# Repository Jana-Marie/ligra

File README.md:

# ligra

ligra is an open source image projector build from scratch and based off of flea market parts. ligra is not neccessarily a PCB-project nor a single thing, but rather an idea of how to design your own image-projection system. It is an introduction on how to create light-grafittis, how to share messages at large.

It's not strictly a Gobo, rather a way of building a system that may resemble one, but may also resemble a video projector or an abstract source of art. I have mostly used it with 2D printed stencils, usually used with so called "overhead projectors", one can of course also use metal-stencils, coloured effect-foils, 3D printed stencils and even LCDs, or really anything that may project an image. Get creative! 

<table>
  <tbody>
    <tr>
      <td>
        
      </td>
      <td>
        
      </td>
    </tr>
    <tr>
      <td colspan="2">
        
      </td>
    </tr>
  </tbody>
</table>

This repo is very WIP and shall be expanded soon :3

## Working principle

ligra essentially functions as a backwards camera, well, most projectors do. This becomes more visible when we talk about its inner workings, it's heart and most fixed element is the lens, a Canon FD lens in our case. But instead of using it to project and image **onto** a 35mm film slide, we will project light **through** a ruffly 35mm film slide-sized, image forming medium (i.e. a 2D printed stencil). This light will enter the lens from the back, projecting an image onto a scene with the properties of the lens (focal length, aperture and focus). Given the quality of even early lenses, we can expect some sharp and crisp projections. [WIP ...]

## [Instructions](https://github.com/Jana-Marie/ligra/blob/main/instructions.md)

(Want to build one? ^ click me)

<table>
  <tbody>
    <tr>
      <td>
        
      </td>
    </tr>
  </tbody>
</table>

## [Projection-Media](https://github.com/Jana-Marie/ligra/blob/main/projection-media.md)

(You have one and need stencils? ^ click me)

<table>
  <tbody>
    <tr>
      <td>
        
      </td>
      <td>
        
      </td>
      <td>
        
      </td>
    </tr>
  </tbody>
</table>

## [Staging-Stages](https://github.com/Jana-Marie/ligra/blob/main/staging-stages.md)

(You have one and want to work on a different stage, a different way of adding media for projection? ^ click me)

<table>
  <tbody>
    <tr>
      <td>
        
      </td>
      <td>
        
      </td>
      <td>
        
      </td>
    </tr>
  </tbody>
</table>

## Todo

- [ ] Add assembly instructions (85% done)
  - [ ] Refine by adding real images (45% done)
- [ ] Add 3D print instructions (5% done)
- [ ] Add BOM (0% done)
- [ ] Add drawings (60% done)
- [x] Make projection-media page more expressive
- [x] Design more stages
- [x] Cleanup OpenSCAD file

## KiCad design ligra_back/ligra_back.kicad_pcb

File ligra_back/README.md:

# Back-Board

This board serves as power-input and LED controller for a 0-3A 0-5V LED. It currently is v1.0.0 and has an additional DC-motor speed controller onboard, you can safely ignore it. I plan to build a different version for myself, that is a bit more advanced, feel free to then also use it. Generally this board is fully optional, but may prove to be very useful.

<table>
  <tbody>
    <tr>
      <td>
        
      </td>
      <td>
        
      </td>
    </tr>
  </tbody>
</table>

[Todo, add BOM and assembly instructions here]

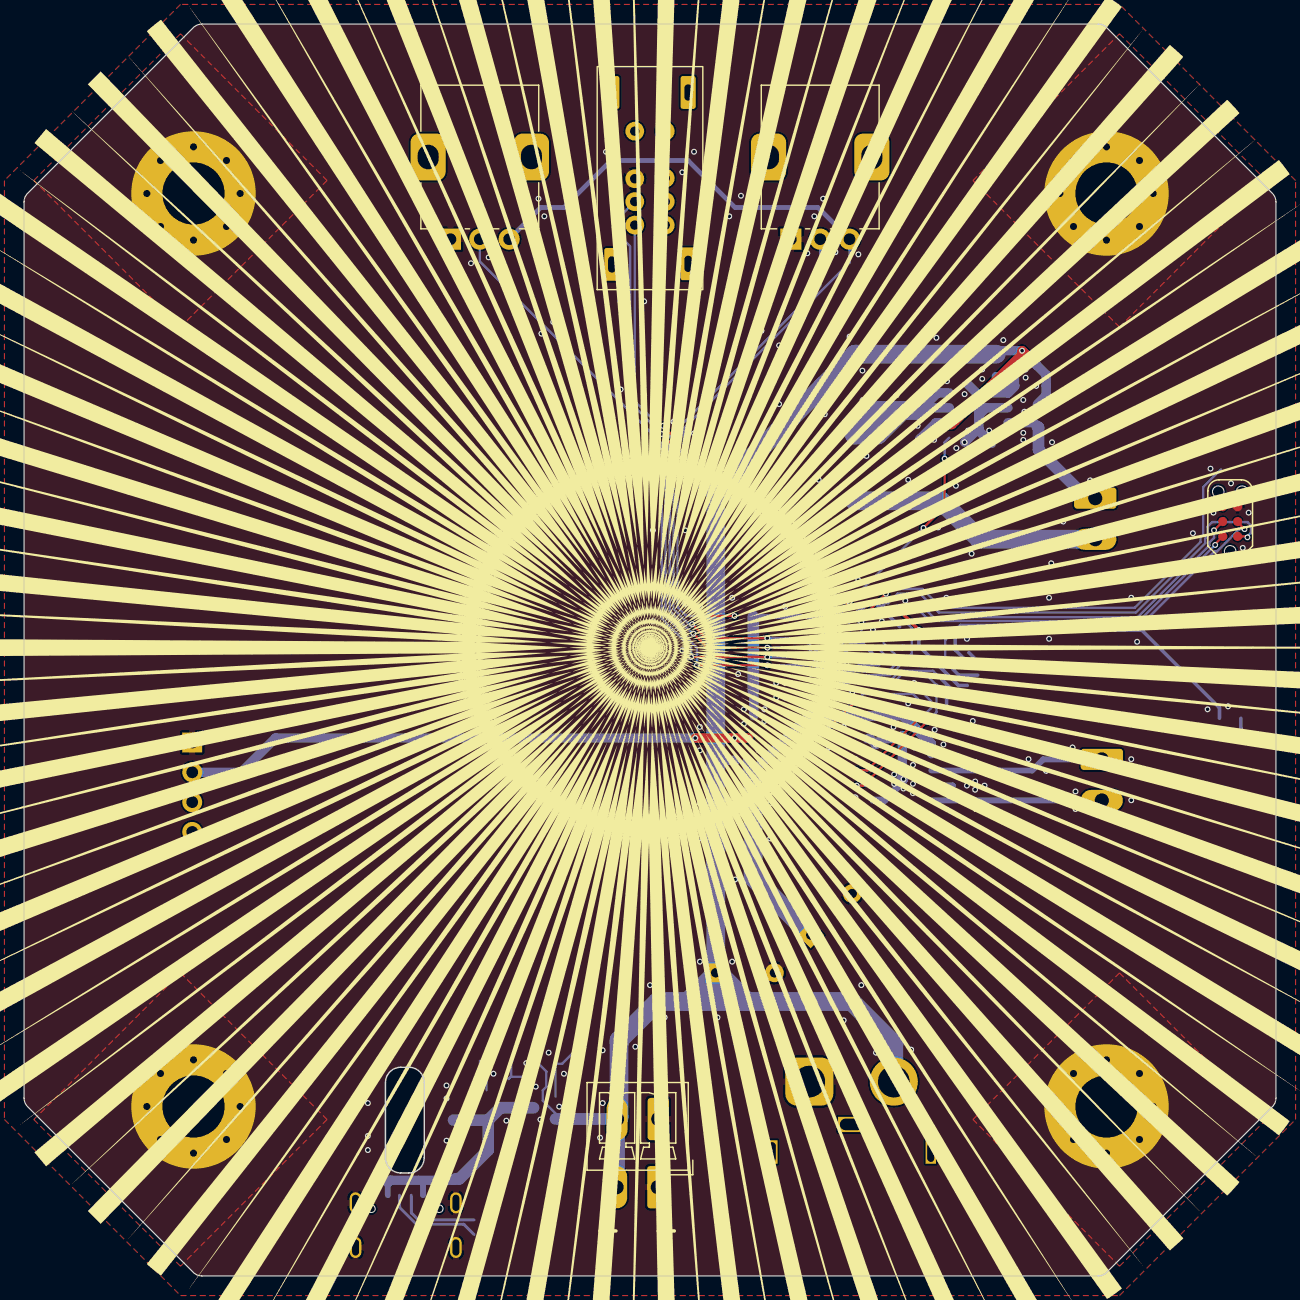
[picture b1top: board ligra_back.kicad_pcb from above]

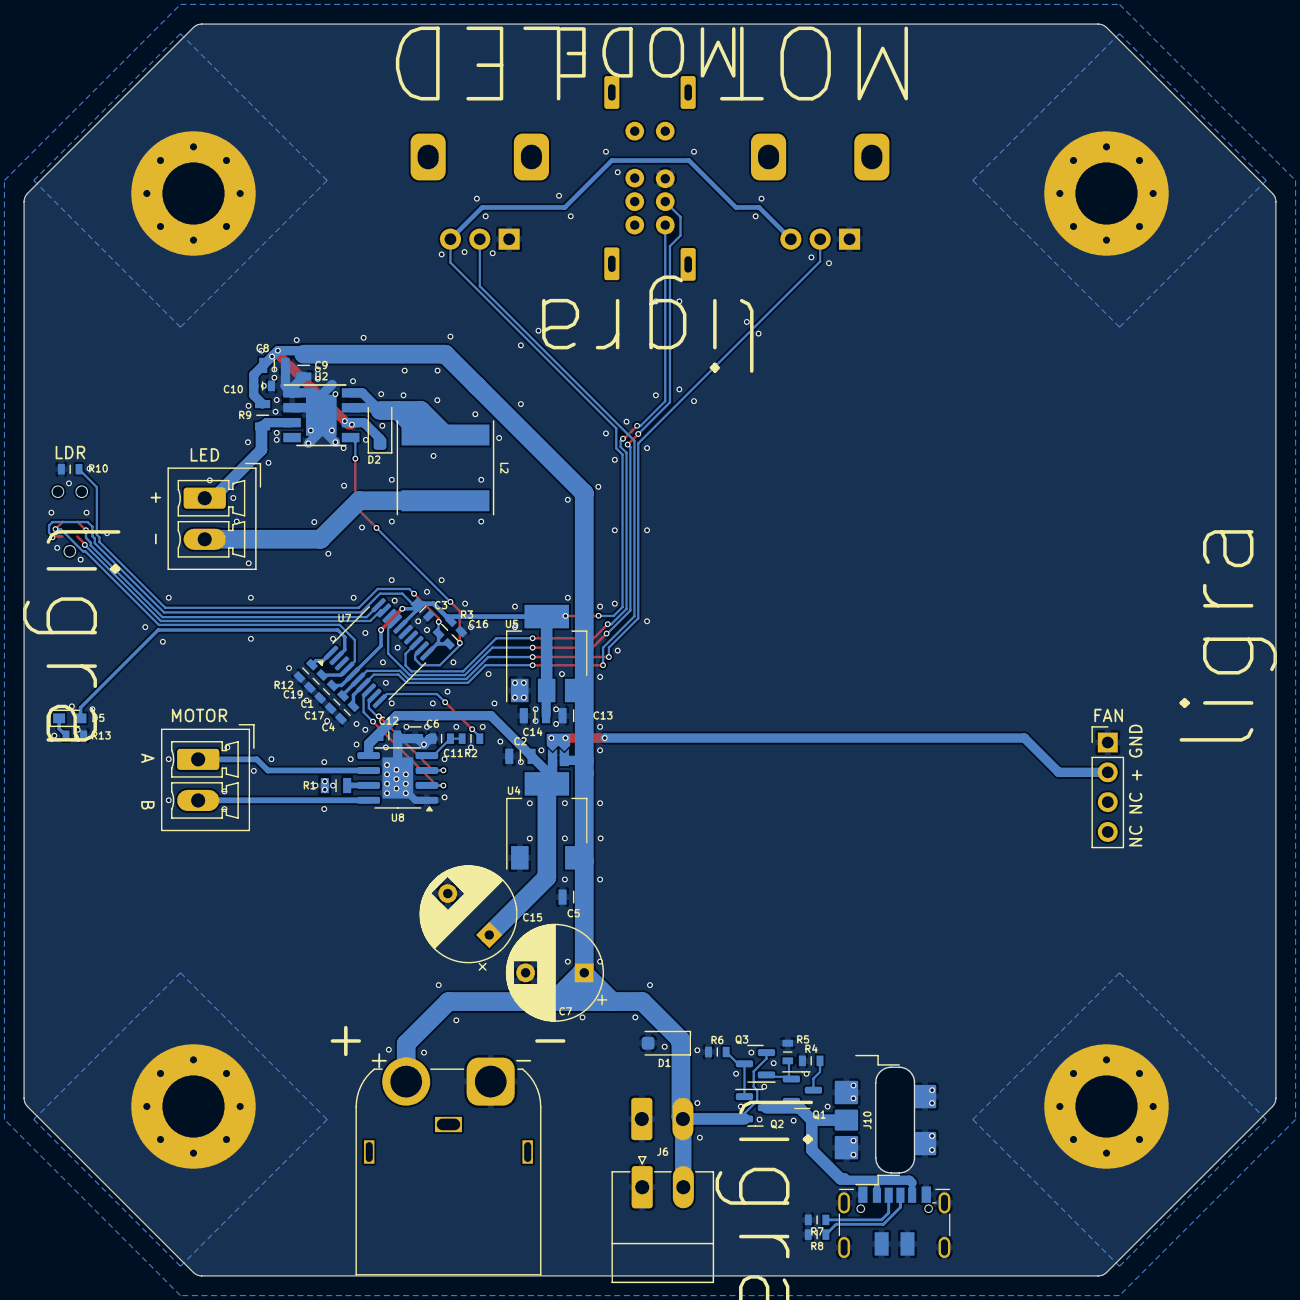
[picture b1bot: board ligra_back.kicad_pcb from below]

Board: 2 copper layers, 106.7 x 106.7 mm, 59 parts (50 on the bottom side), 33 nets.

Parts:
C1, C3, C4, C10, C11, C12, C16, C17, C19: 100n; C_0603
C2, C5, C6, C8, C9, C13, C14: 4u7; C_0805
C7, C15: 100u; CP_Radial_D8.0mm_P5.00mm
D1, D2: D210; D_SOD-123F
D5: LED; LED_0603_1608Metric
J1, J2, J3, J4: Mount; MountingHole_5.3mm_M5_Pad_Via
J5: POWER; PhoenixContact_MCV_1,5_2-G-3.5_1x02_P3.50mm_Vertical
J6: POWER; PhoenixContact_MC_1,5_2-G-3.5_1x02_P3.50mm_Horizontal
J7: LED; PhoenixContact_MCV_1,5_2-G-3.5_1x02_P3.50mm_Vertical
J8: FAN; PinHeader_1x04_P2.54mm_Vertical
J9: Motor; PhoenixContact_MCV_1,5_2-G-3.5_1x02_P3.50mm_Vertical
J10: USB-vertical_footprint; USB-C-vertical_footprint
J11: USB_C_Receptacle_PowerOnly_6P; USB-C_Power
J12: XT60; AMASS_XT60IPW-M_1x03_P7.20mm_Horizontal
JP1: jmp; JMP_2_1
L2: 47uF; L_Taiyo-Yuden_NR-80xx
P1: TC2030-CTX-Tag-Connect; TC2030
Q1, Q3: BC807; SOT-23
Q2: AO3401A; SOT-23
R1, R9: R33; R_0805
R2, R3, R4, R5, R6, R7, R8, R12, R13: 5k1; R_0603
R10: LDR; R_0603
RV1, RV2: 10k; Potentiometer_Alps_RK09K_Single_Vertical
SW2: SW_SP3T; SW_3S
U2: AL8843; Diodes_SO-8EP
U4: NCP1117-12_SOT223; SOT-223-3_TabPin2
U5: NCP1117-3.3_SOT223; SOT-223-3_TabPin2
U7: STM32F030F4Px; TSSOP-20_4.4x6.5mm_P0.65mm
U8: DRV8231; SOIC-8-1EP_3.9x4.9mm_P1.27mm_EP2.62x3.51mm

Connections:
+3V3: C1.2, C3.2, C14.2, P1.1 (VCC), R3.2, RV1.3, RV2.3, U5.2 (VO), U7.5 (VDDA), U7.16 (VDD)
+12V: C2.2, C6.2, C12.1, C15.1, JP1.1 (A), U4.2 (VO), U8.5 (VM)
GND: C1.1, C2.1, C3.1, C4.1, C5.1, C6.1, C7.2, C8.1, C9.1, C10.1, C11.1, C12.2, C13.2, C14.1, C15.2, C16.1, C17.1, C19.1, D1.2 (A), J1.1, J2.1, J3.1, J4.1, J5.1, J6.1, J8.1, J10.1 (GND), J10.S1 (GND), J11.A12 (GND), J11.B12 (GND), J11.S1 (SHIELD), J12.1, P1.5 (GND), R1.2, R4.1, R5.1, R6.1, R7.2, R8.2, R10.1, R12.1, R13.1, RV1.1, RV2.1, SW2.3, U2.1 (GND), U2.2 (GND), U2.9 (GND), U4.1 (GND), U5.1 (GND), U7.15 (VSS), U8.1 (GND), U8.9 (GND)
LED_CONTROL: U2.5 (CTRL), U7.12 (PA6)
NRST: C19.2, P1.3 (~RESET), U7.4 (NRST)
unnamed: D2.2 (A), L2.1, U2.7 (SW), U2.8 (SW)
unnamed: D5.2 (A), U7.2 (PF0)
unnamed: D5.1 (K), R13.2
unnamed: J7.1, R9.2, U2.3 (SET)
unnamed: J7.2, L2.2
unnamed: J8.2, JP1.2 (C)
unnamed: J9.1, U8.6 (OUT1)
unnamed: J9.2, U8.8 (OUT2)
unnamed: J10.2 (VBUS), J11.A9 (VBUS), J11.B9 (VBUS), Q1.2 (E), Q2.3 (D)
unnamed: J11.A5 (CC1), R7.1
unnamed: J11.B5 (CC2), R8.1
unnamed: Q1.1 (B), Q3.1 (B), R5.2
unnamed: Q1.3 (C), R4.2
unnamed: Q2.1 (G), Q3.3 (C), R6.2
unnamed: R12.2, U7.1 (BOOT0)
unnamed: C17.2, RV2.2, U7.6 (PA0)
unnamed: C4.2, RV1.2, U7.7 (PA1)
unnamed: U7.8 (PA2), U8.2 (IN2)
unnamed: U7.9 (PA3), U8.3 (IN1)
unnamed: R2.1, U7.10 (PA4)
unnamed: C16.2, R3.1, R10.2, U7.11 (PA5)
unnamed: SW2.1, U7.13 (PA7)
unnamed: SW2.2, U7.17 (PA9)
unnamed: R1.1, U8.7 (ISEN)
unnamed: C11.2, R2.2, U8.4 (VREF)
SWCLK: P1.4 (SWCLK/TCK), U7.20 (PA14)
SWDIO: P1.2 (SWDIO/TMS), U7.19 (PA13)
VBUS: C5.2, C7.1, C8.2, C9.2, C10.2, C13.1, D1.1 (K), D2.1 (K), J5.2, J6.2, J12.2, JP1.3 (B), Q2.2 (S), Q3.2 (E), R9.1, U2.6 (VIN), U4.3 (VI), U5.3 (VI)

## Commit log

2024-06-01 added gitignore
2024-06-01 added images
2024-06-01 added ligra pcbs
2024-06-01 added 3D files
2024-06-14 added PCB graphics
2024-06-14 added more images
2024-06-14 added pcb readmes
2024-06-14 removed images
2024-06-14 added more stls
2024-06-14 added first instructions, not zet finished
2024-06-14 updated gitignore
2024-06-14 fixed tzpos
2024-06-14 added license
2024-06-14 fixed spacing
2024-06-14 added more links
2024-06-14 big CAD refactor, CAD cleanup
2024-06-14 worked on instructions
2024-06-14 removed old files
2024-06-14 updated images
2024-06-14 cleaned up stage
2024-06-14 updated instructions
2024-06-15 added stage instructions
2024-06-15 updated stage
2024-06-15 fixed typo
2024-06-15 added two more images
2024-06-15 added flashlight
2024-06-15 worked on the lensmount
2024-06-15 added stencil svg
2024-06-15 added projection media
2024-06-15 added staging-stages
2024-06-15 worked on stages
2024-06-15 added description
2024-06-15 gramma change
2024-06-15 added pcb, improved view
2024-06-15 added drawing
2024-07-07 updated STLs, added new ones, removed old oneas
2024-07-07 updated back to v1.2.0
2025-01-04 added lava-disk
2025-01-04 updated files
2025-01-04 added more lens stls
2025-01-04 added interlock
2025-01-04 added more projection media
2025-01-04 TOC projection media
2025-01-04 fixed images
2025-01-04 added header image
2025-01-04 make more pretty
2025-01-04 added more instructions
